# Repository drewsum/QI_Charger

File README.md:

# QI_Charger

A DIY QI Wireless Phone Charger with Digital Monitoring, OLED Display, and USB Virtual COM Port

Made with KiCad 5.0.2

Requires drewsum's 'KiCad_Custom_Libraries' git repository for custom symbols and footprints

Microcontroller U503 is programmed via header J401 using PIC KIT 3, with firmware located at sfw/U503_Firmware/QI_Monitor.X

Built with Microchip compiler XC8 V1.45, IDE MPLAB V5.15

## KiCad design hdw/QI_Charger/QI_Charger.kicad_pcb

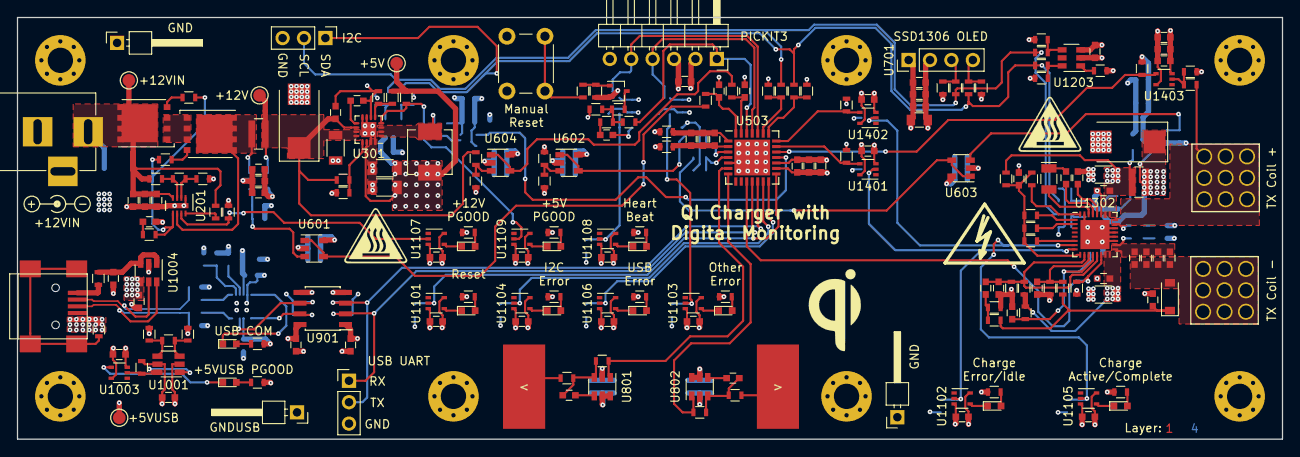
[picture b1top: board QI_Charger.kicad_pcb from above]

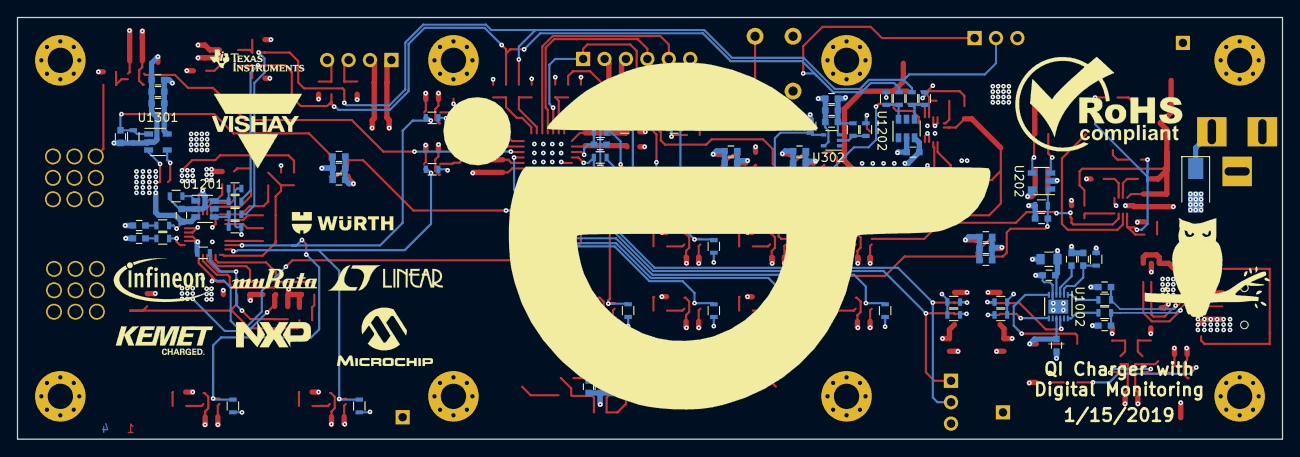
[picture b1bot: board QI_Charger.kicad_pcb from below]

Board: 4 copper layers, 150.0 x 50.0 mm, 305 parts (87 on the bottom side), 137 nets.

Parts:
C201, C204, C205, C303, C304, C401, C402, C501, C502, C503, C506, C601, C602, C609, C613, C701, C807, C808, C901, C902, C1001, C1002, C1003, C1004, C1005, C1007, C1008, C1011, C1101, C1102, C1103, C1104, C1105, C1106, C1107, C1108, C1109, C1201, C1202, C1203, C1301, C1309, C1311, C1314, C1316, C1401, C1403, C1404: 0.1uF; C_0603
C202, C206, C302, C305, C504, C507, C603, C604, C607, C608, C610, C612, C614, C616, C702, C801, C802, C805, C806, C1302, C1310, C1312, C1319, C1402: 10nF; C_0603
C203, C207, C208, C306, C505, C508, C605, C606, C611, C615, C703, C803, C804, C1303, C1304, C1306, C1317, C1405: 1nF; C_0603
C209, C1323: 100uF; CP_Tantalum_Case-X_EIA-7343-43_Reflow
C301: 10uF; C_1206
C307, C308, C1307, C1308: 22uF; C_1206
C704: 1uF; C_0805
C1006: 4.7uF; C_0805
C1009, C1010: 47pF; C_0603
C1305: 2.2pF; C_0603
C1313, C1315: 6.8nF; C_0603
C1318, C1322: 22nF; C_0603
C1320, C1321: 82nF; C_0603
D201: 24V; D_SMA
D1001, D1105, D1107, D1108, D1109: Green; LED_0603
D1002: Yellow; LED_0603
D1101, D1102, D1103, D1104, D1106: Red; LED_0603
D1301: MBR0530; D_SOD-123
H1501, H1502, H1503, H1504, H1505, H1506, H1507, H1508: 3mm Mounting Hole; MountingHole_3mm_Pad_Via
J201: +12V IN; BARREL_JACK
J401: PICKIT3; PICKIT3_Header
J701: I2C; Pin_Header_Straight_1x03_Pitch2.54mm
J901: UART; Pin_Header_Straight_1x03_Pitch2.54mm
J1001: USB_B_Mini; USB_Mini-B
J1301, J1302: PAD; Wuerth_7461096_M4_Shank_9pos
L301: 2.2u; L_Vishay_IHLP-2020
L501, L502, L1001, L1002: 600R 0.5A; L_0603
Q201, Q202: IPC100N04S51R7ATMA1; TDSON-8-1
Q401: BSS214NW; SOT-323_SC-70
R201: 6.04M; R_0603
R202: 86.6k; R_0603
R203: 243k; R_0603
R204, R302, R305, R1308, R1404: 100k; R_0603
R205, R206, R401: 10; R_0603
R207, R301, R308, R402, R404, R503, R504, R505, R506, R601, R602, R606, R703, R704, R901, R902, R903, R904, R1001, R1005, R1101, R1102, R1103, R1107, R1108, R1111, R1114, R1207, R1208, R1209, R1210, R1211, R1212, R1213, R1214, R1306, R1401, R1402, R1405, R1406, R1407: 10k; R_0603
R208, R607: 5.1k; R_0603
R209, R1303: 0.02; R_0612
R210: 499k; R_0603
R303, R306: 10.5k; R_0603
R304, R1304: 249k; R_0603
R307: 2k; R_0603
R403: 100; R_0603
R405, R501, R502, R701, R702, R803, R804, R1201, R1202, R1203, R1204, R1205, R1206: 0; R_0603
R406, R1006, R1009, R1104, R1105, R1106, R1109, R1110, R1112, R1113, R1115, R1116, R1403: 1k; R_0603
R603, R604, R605, R608, R801, R802: 499; R_0603
R1002: 487k; R_0603
R1003: 6.04k; R_0603
R1004: 40.2k; R_0603
R1007, R1008: 27; R_0603
R1301, R1302: 390k; R_0603
R1305: 47k; R_0603
R1307: 43k; R_0603
R1309: 130k; R_0603
R1310: 1M; R_0603
R1311, R1314, R1316: 15k; R_0603
R1312, R1313: 1; R_0603
R1315: 1.8k; R_0603
R1317: 27k; R_0603
SW401: MRST; SW_PUSH_6mm
SW801, SW802: Cap_Touch; Capacitive_Touch_Pad
TH1301: 100k; R_0603
TP201, TP204, TP1002: TP; Pin_Header_Angled_1x01_Pitch2.54mm
TP202, TP203, TP301, TP1001: TP; Test_Point
U201: LTC4365DDB; DFN-8-1EP_2x3mm_Pitch0.5mm
U202, U1301: INA138; SOT-23-5
U301: TPS62130; QFN-16-1EP_3x3mm_Pitch0.5mm
U302, U501, U502, U1403: 74LVC1G17; SOT-353_SC-70-5
U503: PIC18F27K40T-I_ML; QFN-28-1EP_6x6mm_Pitch0.65mm
U601, U602, U603, U604: OPA340NA; SOT-23-5
U701: SSD1306; Pin_Header_Straight_1x04_Pitch2.54mm
U801, U802: AT42QT1010-TSHR; SOT-23-6
U901: ISO7321C; SOIC-8_3.9x4.9mm_Pitch1.27mm
U1001: LT6700-1-S6; TSOT-23-6
U1002: FT234XD; DFN-12-1EP_3x3mm_Pitch0.45mm
U1003, U1101, U1103, U1104, U1106, U1107, U1108, U1109: 74LVC1G06; SOT-353_SC-70-5
U1004: TPD3S014DBVR; SOT-23-6
U1102, U1105: 74LVC1G07; SOT-353_SC-70-5
U1201, U1202, U1203: LM73-1; SOT-23-6
U1302: NXQ1TXH5_101J; QFN-32-1EP_5x5mm_Pitch0.5mm
U1401, U1402: 74LVC1G14; SOT-353_SC-70-5
Y1301: 32.768kHz; Crystal_SMD_G8-2pin_3.2x1.5mm

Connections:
+5V: C205.1, C206.1, C207.1, C304.1, C305.1, C306.1, C307.1, C308.1, C401.1, C502.1, C503.1, C506.1, C507.1, C508.1, C601.1, C602.1, C603.1, C604.1, C605.1, C606.1, C609.1, C610.1, C611.1, C613.1, C614.1, C615.1, C701.1, C702.1, C703.1, C704.1, C803.1, C804.1, C805.1, C806.1, C807.1, C808.1, C901.1, C1101.1, C1102.1, C1103.1, C1104.1, C1105.1, C1106.1, C1107.1, C1108.1, C1109.1, C1201.1, C1202.1, C1203.1, C1301.1, C1302.1, C1304.1, C1323.1, C1401.1, C1402.1, C1403.1, C1404.1, C1405.1, J401.2, L301.2, L501.2, R207.1, R301.1, R306.1, R404.1, R503.1, R504.1, R601.2, R703.1, R704.1, R901.2, R902.2, R1101.1, R1102.1, R1104.1, R1105.1, R1106.1, R1108.1, R1109.1, R1110.1, R1112.1, R1113.1, R1115.1, R1116.1, R1207.1, R1208.1, R1209.1, R1210.1, R1211.1, R1212.1, R1214.1, R1303.1, R1401.2, R1402.2, SW401.1, TP301.1, U202.5, U301.14, U302.5, U501.5, U502.5, U503.17, U601.5, U602.5, U603.5, U604.5, U701.1, U801.5, U801.6, U802.5, U802.6, U901.1, U1101.5, U1102.5, U1103.5, U1104.5, U1105.5, U1106.5, U1107.5, U1108.5, U1109.5, U1201.3, U1202.3, U1203.3, U1301.3, U1301.5, U1401.5, U1402.5, U1403.5
+5VADC: C501.1, C504.1, C505.1, L501.1, U503.2
+5VP: C1307.1, C1308.1, C1310.1, C1312.1, R1301.1, R1303.2, R1308.1, R1310.1, U1301.4, U1302.15, U1302.16, U1302.25, U1302.26
+5V_USB: C902.1, C1002.1, C1003.1, C1004.1, C1005.1, C1006.1, C1008.1, R903.2, R904.2, R1001.1, R1002.1, R1005.1, R1006.1, R1009.1, TP1001.1, U901.8, U1001.5, U1002.4, U1002.9, U1003.5, U1004.4
+12V: C209.1, C301.1, C303.1, R209.2, R302.1, R606.2, TP203.1, U202.4, U301.10, U301.11, U301.12
+12Vin: C201.1, C202.1, C203.1, D201.1, J201.1, Q201.5, R201.1, R204.1, TP202.1, U201.4
/Microcontroller/PIC_I2C_SCL: R502.1, R503.2, U503.23
/Microcontroller/PIC_I2C_SDA: R501.2, R504.2, U503.22
/OLED Display/OLED_I2C_SCL: R702.1, R703.2, U701.3
/OLED Display/OLED_I2C_SDA: R701.2, R704.2, U701.4
/Temperature Sensors/Temp1_I2C_SCL: R1202.1, R1207.2, U1201.4
/Temperature Sensors/Temp1_I2C_SDA: R1201.2, R1210.2, U1201.6
/Temperature Sensors/Temp2_I2C_SCL: R1204.1, R1208.2, U1202.4
/Temperature Sensors/Temp2_I2C_SDA: R1203.2, R1211.2, U1202.6
/Temperature Sensors/Temp3_I2C_SCL: R1206.1, R1209.2, U1203.4
/Temperature Sensors/Temp3_I2C_SDA: R1205.2, R1212.2, U1203.6
/USB UART Bridge/BRIDGE_USB+: R1007.2, U1002.12
/USB UART Bridge/BRIDGE_USB-: R1008.2, U1002.1
/USB UART Bridge/CONN_USB+: C1009.1, J1001.3, R1007.1, U1004.6
/USB UART Bridge/CONN_USB-: C1010.1, J1001.2, R1008.1, U1004.5
/USB UART Bridge/POS5_USB_PGOOD: R1005.2, U1001.1, U1001.6, U1003.2
Cap_Touch_Left: R803.2, U503.6, U801.1
Cap_Touch_Right: R804.2, U503.7, U802.1
GND: C201.2, C202.2, C203.2, C204.2, C205.2, C206.2, C207.2, C208.2, C209.2, C301.2, C302.2, C303.2, C304.2, C305.2, C306.2, C307.2, C308.2, C401.2, C402.2, C502.2, C503.2, C506.2, C507.2, C508.2, C601.2, C602.2, C603.2, C604.2, C605.2, C606.2, C607.2, C608.2, C609.2, C610.2, C611.2, C612.2, C613.2, C614.2, C615.2, C616.2, C701.2, C702.2, C703.2, C704.2, C803.2, C804.2, C805.2, C806.2, C807.2, C808.2, C901.2, C1101.2, C1102.2, C1103.2, C1104.2, C1105.2, C1106.2, C1107.2, C1108.2, C1109.2, C1201.2, C1202.2, C1203.2, C1301.2, C1302.2, C1303.2, C1304.2, C1306.2, C1307.2, C1308.2, C1309.2, C1310.2, C1311.2, C1312.2, C1313.2, C1315.2, C1317.2, C1318.2, C1322.2, C1323.2, C1401.2, C1402.2, C1403.2, C1404.2, C1405.2, D201.2, J201.2, J201.3, J401.3, J701.3, J901.3, L502.2, Q401.2, R203.2, R210.2, R303.2, R305.2, R307.2, R308.2, R402.2, R505.2, R506.2, R602.1, R607.2, R1103.2, R1107.2, R1111.2, R1114.2, R1213.2, R1304.2, R1306.2, R1311.2, R1314.2, R1315.2, R1404.2, R1405.2, R1406.1, R1407.1, TH1301.2, TP201.1, TP204.1, U201.1, U201.9, U202.2, U301.6, U301.7, U301.8, U301.15, U301.16, U301.17, U302.3, U501.3, U502.3, U503.5, U503.16, U503.29, U601.2, U602.2, U603.2, U604.2, U701.2, U801.2, U802.2, U901.4, U1101.3, U1102.3, U1103.3, U1104.3, U1105.3, U1106.3, U1107.3, U1108.3, U1109.3, U1201.2, U1202.2, U1203.2, U1301.2, U1302.19, U1302.20, U1302.21, U1302.22, U1302.27, U1302.31, U1302.33, U1401.3, U1402.3, U1403.3
GNDA: C501.2, C504.2, C505.2, L502.1, U503.1
GND_USB: C902.2, C1001.2, C1002.2, C1003.2, C1004.2, C1005.2, C1006.2, C1007.2, C1008.2, C1009.2, C1010.2, C1011.2, J1001.5, L1002.1, R1004.2, TP1002.1, U901.5, U1001.2, U1002.5, U1002.13, U1003.3, U1004.2
Heartbeat_LED: R505.1, R1114.1, U501.4, U1108.2
I2C_Error_LED: R1107.1, U503.13, U1104.2
I2C_SCL: J701.2, R502.2, R702.2, R1202.2, R1204.2, R1206.2
I2C_SDA: J701.1, R501.1, R701.1, R1201.1, R1203.1, R1205.1
ICSPCLK: J401.5, U501.2, U503.24
ICSPDAT: J401.4, U502.2, U503.25
unnamed: C204.1, R208.2
unnamed: C302.1, U301.9
unnamed: C402.1, R405.2
unnamed: C801.1, U801.4
unnamed: C801.2, R801.2, R803.1, U801.3
unnamed: C802.1, U802.4
unnamed: C802.2, R802.2, R804.1, U802.3
unnamed: C1001.1, R1001.2, U1002.2
unnamed: C1007.1, U1002.3
unnamed: C1011.1, L1001.2, U1004.1, U1004.3
unnamed: C1303.1, R1301.2, R1302.1, R1305.1, R1307.1, R1309.1, U1302.9
unnamed: C1305.2, Y1301.1
unnamed: C1309.1, U1302.28
unnamed: C1313.1, R1312.2
unnamed: C1314.1, C1316.1, C1320.1, C1321.1, D1301.2, J1302.1
unnamed: C1314.2, C1316.2, C1320.2, C1321.2, R1313.1, U1302.17, U1302.18
unnamed: C1315.1, R1313.2
unnamed: C1317.1, C1319.1, R1310.2, R1311.1, U1302.10, U1302.13
unnamed: C1318.1, R1315.1, R1317.2, U1302.11
unnamed: C1319.2, R1314.1, R1316.2
unnamed: C1322.1, D1301.1, R1316.1, R1317.1
unnamed: D1001.1, U1003.4
unnamed: D1001.2, R1006.2
unnamed: D1002.2, R1009.2
unnamed: D1101.1, U1101.4
unnamed: D1101.2, R1104.2
unnamed: D1102.1, U1102.4
unnamed: D1102.2, R1105.2
unnamed: D1103.1, U1103.4
unnamed: D1103.2, R1106.2
unnamed: D1104.1, U1104.4
unnamed: D1104.2, R1109.2
unnamed: D1105.1, U1105.4
unnamed: D1105.2, R1110.2
unnamed: D1106.1, U1106.4
unnamed: D1106.2, R1112.2
unnamed: D1107.1, U1107.4
unnamed: D1107.2, R1113.2
unnamed: D1108.1, U1108.4
unnamed: D1108.2, R1115.2
unnamed: D1109.1, U1109.4
unnamed: D1109.2, R1116.2
unnamed: J1001.1, L1001.1
unnamed: J1001.6, L1002.2
unnamed: L301.1, R304.1, U301.1, U301.2, U301.3
unnamed: Q201.1, Q201.2, Q201.3, Q202.1, Q202.2, Q202.3
unnamed: Q201.4, R205.2
unnamed: Q202.4, R206.1
unnamed: Q202.5, R209.1, U201.6, U202.3
unnamed: Q401.1, R401.2, R402.1
unnamed: Q401.3, R403.2
unnamed: R201.2, R202.1, U201.3
unnamed: R202.2, R203.1, U201.2
unnamed: R204.2, U201.8
unnamed: R205.1, R206.2, R208.1, U201.5
unnamed: R302.2, R303.1, U301.13
unnamed: R304.2, R305.1, U302.2
unnamed: R306.2, R307.1, U301.5
unnamed: R401.1, SW401.2
unnamed: R403.1, R404.2, R405.1, R406.2
unnamed: R601.1, R602.2, U602.3
unnamed: R603.2, U601.1, U601.4
unnamed: R604.2, U602.1, U602.4
unnamed: R605.2, U603.1, U603.4
unnamed: R606.1, R607.1, U604.3
unnamed: R608.2, U604.1, U604.4
unnamed: R801.1, SW801.1
unnamed: R802.1, SW802.1
unnamed: R1002.2, R1003.1, U1001.3
unnamed: R1003.2, R1004.1, U1001.4
unnamed: R1213.1, U1201.1
unnamed: R1214.2, U1203.1
unnamed: R1302.2, U1302.32
unnamed: R1305.2, U1302.1
unnamed: R1307.2, U1302.2
unnamed: R1309.2, U1302.6
unnamed: R1403.2, R1404.1, U1403.2
Other_Error_LED: R506.1, R1103.1, U502.4, U1103.2
POS5_ADC: C608.1, R604.1, U503.3
POS5_PGOOD: R301.2, U301.4, U1109.2
POS5_SW_SNS: R308.1, U302.4, U503.18
POS12_ADC: C616.1, R608.1, U503.27
POS12_ISNS: C208.1, R210.1, U202.1, U601.3
POS12_ISNS_ADC: C607.1, R603.1, U503.28
POS12_PGOOD: R207.2, U201.7, U1107.2
QI_Charge: R1407.2, U503.21, U1402.4
QI_ISNS: C1306.1, R1304.1, U603.3, U1301.1
QI_ISNS_ADC: C612.1, R605.1, U503.4
QI_Idle: R1406.2, U503.20, U1401.4
QI_LED_G: R1108.2, R1402.1, U1105.2, U1302.7, U1402.2
QI_LED_R: R1102.2, R1401.1, U1102.2, U1302.8, U1401.2
QI_NTC: C1311.1, R1308.2, TH1301.1, U1302.12
QI_OSC_1: C1305.1, U1302.29
QI_OSC_2: U1302.30, Y1301.2
QI_SW: J1301.1, R1312.1, R1403.1, U1302.23, U1302.24
QI_SW_SNS: R1405.1, U503.19, U1403.4
QI_Standby: R1306.1, U503.10, U1302.14
USB_Error_LED: R1111.1, U503.14, U1106.2
USB_UART_RX: J901.1, R901.1, U503.11, U901.2
USB_UART_RX_ISO: R904.1, U901.7, U1002.7
USB_UART_TX: J901.2, R902.1, U503.12, U901.3
USB_UART_TX_ISO: R903.1, U901.6, U1002.10
~ACTIVE_LED: R1101.2, U503.15, U1101.2
~MCLR: J401.1, R406.1, U503.26
~USB_ACTIVE: D1002.1, U1002.6

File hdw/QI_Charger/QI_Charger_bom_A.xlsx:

References | Value | Quantity Per PCB | Digi-Key PN
C201 C204 C205 C303 C304 C401 C402 C501 C502 C503 C506 C601 C602 C609 C613 C701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 | 0.1uF | 48 | 311-1344-1-ND
C209 C1323 | 100uF | 2 | 718-1102-1-ND
C202 C206 C302 C305 C504 C507 C603 C604 C607 C608 C610 C612 C614 C616 C702 C801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 | 10nF | 24 | 1276-1921-1-ND
C301 | 10uF | 1 | 1276-7031-1-ND
C203 C207 C208 C306 C505 C508 C605 C606 C611 C615 C703 C803 C804 C1303 C1304 C1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 | 1nF | 18 | 1276-1018-1-ND
C704 | 1uF | 1 | 490-1695-1-ND
C1305 | 2.2pF | 1 | 1276-1281-1-ND
C1318 C1322 | 22nF | 2 | 399-1280-1-ND
C307 C308 C1307 C1308 | 22uF | 4 | 1276-3148-1-ND
C1006 | 4.7uF | 1 | 1276-2972-1-ND
C1009 C1010 | 47pF | 2 | 478-1171-1-ND
C1313 C1315 | 6.8nF | 2 | 399-9121-1-ND
C1320 C1321 | 82nF | 2 | 478-10362-1-ND
D201 | 24V | 1 | SMAJ24CALFCT-ND
D1001 D1105 D1107 D1108 D1109 | Green | 5 | 160-1446-1-ND
D1301 | MBR0530 | 1 | MBR0530T1GOSCT-ND
D1101 D1102 D1103 D1104 D1106 | Red | 5 | 160-1447-1-ND
D1002 | Yellow | 1 | 160-1448-1-ND
DOC701 | 0x3C | 1
DOC1202 | 0x4C | 1
DOC1201 | 0x4D | 1
DOC1203 | 0x4F | 1
DOC1001 | COM_Port_Settings | 1
DOC501 | Master | 1
J201 | +12V IN | 1 | CP-202BH-ND
J1301 J1302 | PAD | 2 | 732-3214-ND
J401 | PICKIT3 | 1
J1001 | USB_B_Mini | 1 | 732-2109-1-ND
L301 | 2.2u | 1 | 541-1236-1-ND
L1301 | 6.3uH | 1 | 732-5284-ND
L501 L502 L1001 L1002 | 600R 0.5A | 4 | 732-2389-1-ND
MK1501 MK1502 MK1507 MK1508 MK1511 MK1512 MK1515 MK1516 | #4-40 Screw | 8 | 36-9900-ND
MK1503 MK1504 MK1505 MK1506 MK1509 MK1510 MK1513 MK1514 | #4-40 Standoff | 8 | 36-1892-ND
Q401 | BSS214NW | 1 | BSS214NWH6327XTSA1CT-ND
Q201 Q202 | IPC100N04S51R7ATMA1 | 2 | IPC100N04S51R7ATMA1CT-ND
R405 R501 R502 R701 R702 R803 R804 R1201 R1202 R1203 R1204 R1205 R1206 | 0 | 13 | 311-0.0GRCT-ND
R209 R1303 | 0.02 | 2 | P16010CT-ND
R1312 R1313 | 1 | 2 | 311-1.00HRCT-ND
R1315 | 1.8k | 1 | CR0603-FX-1801ELFCT-ND
R205 R206 R401 | 10 | 3 | YAG3351CT-ND
R303 R306 | 10.5k | 2 | 311-10.5KHRCT-ND
R403 | 100 | 1 | A106047CT-ND
R204 R302 R305 R1308 R1404 | 100k | 5 | A106046CT-ND
R207 R301 R308 R402 R404 R503 R504 R505 R506 R601 R602 R606 R703 R704 R901 R902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 | 10k | 41 | RMCF0603FT10K0CT-ND
R1309 | 130k | 1 | 311-130KHRCT-ND
R1311 R1314 R1316 | 15k | 3 | 311-15.0KHRCT-ND
R1310 | 1M | 1 | 311-1.00MHRCT-ND
R406 R1006 R1009 R1104 R1105 R1106 R1109 R1110 R1112 R1113 R1115 R1116 R1403 | 1k | 13 | RMCF0603FT1K00CT-ND
R203 | 243k | 1 | 311-243KHRCT-ND
R304 R1304 | 249k | 2 | RMCF0603FT249KCT-ND
R1007 R1008 | 27 | 2 | RMCF0603FT27R0CT-ND
R1317 | 27k | 1 | RMCF0603FT27K0CT-ND
R307 | 2k | 1 | 311-2.00KHRCT-ND
R1301 R1302 | 390k | 2 | 311-390KHRCT-ND
R1004 | 40.2k | 1 | 311-40.2KHRCT-ND
R1307 | 43k | 1 | 311-43.0KHRCT-ND
R1305 | 47k | 1 | 311-47.0KHRCT-ND
R1002 | 487k | 1 | 311-487KHRCT-ND
R603 R604 R605 R608 R801 R802 | 499 | 6 | P499HCT-ND
R210 | 499k | 1 | RMCF0603FT499KCT-ND
R208 R607 | 5.1k | 2 | YAG3621CT-ND
R201 | 6.04M | 1 | 541-6.04MHCT-ND
R201 | 6.04k | 1 | RMCF0603FT6K04CT-ND
R202 | 86.6k | 1 | 311-86.6KHRCT-ND
SW801 SW802 | Cap_Touch | 2
SW401 | MRST | 1
TH1301 | 100k | 1 | P10555CT-ND
U1003 U1101 U1104 U1106 U1107 U1108 U1109 1103 | 74LVC1G06 | 8 | 296-8484-1-ND
U1102 U1105 | 74LVC1G07 | 2 | 296-8486-1-ND
U1401 U1402 | 74LVC1G14 | 2 | 296-11608-1-ND
U302 U501 U502 U1403 | 74LVC1G17 | 4 | 296-11934-1-ND
U801 U802 | AT42QT1010-TSHR | 2 | AT42QT1010-TSHRCT-ND
U1002 | FT234XD | 1 | 768-1178-1-ND
U202 U1301 | INA138 | 2 | INA138NACT-ND
U901 | ISO7321C | 1 | 296-42102-1-ND
U1201 U1202 U1203 | LM73-1 | 3 | LM73CIMK-1/NOPBCT-ND
U1001 | LT6700-1-S6 | 1 | LT6700CS6-1#TRMPBFCT-ND
U201 | LTC4365DDB | 1 | LTC4365IDDB#TRMPBFCT-ND
U1302 | NXQ1TXH5_101J | 1 | 568-12937-1-ND
U601 U602 U603 U604 | OPA340NA | 4 | 296-26275-1-ND
U503 | PIC18F27K40T-I_ML | 1 | PIC18F27K40T-I/MLCT-ND
U701 | SSD1306 | 1
U1004 | TPD3S014DBVR | 1 | 296-38835-1-ND
U301 | TPS62130 | 1 | 296-37878-1-ND
Y1301 | 32.768kHz | 1 | G83270021CT-ND

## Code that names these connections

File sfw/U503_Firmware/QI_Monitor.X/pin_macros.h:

/* Microchip Technology Inc. and its subsidiaries.  You may use this software 
 * and any derivatives exclusively with Microchip products. 
 * 
 * THIS SOFTWARE IS SUPPLIED BY MICROCHIP "AS IS".  NO WARRANTIES, WHETHER 
 * EXPRESS, IMPLIED OR STATUTORY, APPLY TO THIS SOFTWARE, INCLUDING ANY IMPLIED 
 * WARRANTIES OF NON-INFRINGEMENT, MERCHANTABILITY, AND FITNESS FOR A 
 * PARTICULAR PURPOSE, OR ITS INTERACTION WITH MICROCHIP PRODUCTS, COMBINATION 
 * WITH ANY OTHER PRODUCTS, OR USE IN ANY APPLICATION. 
 *
 * IN NO EVENT WILL MICROCHIP BE LIABLE FOR ANY INDIRECT, SPECIAL, PUNITIVE, 
 * INCIDENTAL OR CONSEQUENTIAL LOSS, DAMAGE, COST OR EXPENSE OF ANY KIND 
 * WHATSOEVER RELATED TO THE SOFTWARE, HOWEVER CAUSED, EVEN IF MICROCHIP HAS 
 * BEEN ADVISED OF THE POSSIBILITY OR THE DAMAGES ARE FORESEEABLE.  TO THE 
 * FULLEST EXTENT ALLOWED BY LAW, MICROCHIP'S TOTAL LIABILITY ON ALL CLAIMS 
 * IN ANY WAY RELATED TO THIS SOFTWARE WILL NOT EXCEED THE AMOUNT OF FEES, IF 
 * ANY, THAT YOU HAVE PAID DIRECTLY TO MICROCHIP FOR THIS SOFTWARE.
 *
 * MICROCHIP PROVIDES THIS SOFTWARE CONDITIONALLY UPON YOUR ACCEPTANCE OF THESE 
 * TERMS. 
 */

/* 
 * File:   
 * Author: 
 * Comments:
 * Revision history: 
 */

// This is a guard condition so that contents of this file are not included
// more than once.  
#ifndef _PIN_MACROS_H
#define	_PIN_MACROS_H

#include <xc.h> // include processor files - each processor file is guarded.  

// These are pin macro definitions so that microcontroller I/O can be easily
// accessed instead of reading from/writing to bitfields in registers

// Port A
#define POS12_ADC_PIN           PORTAbits.RA0
#define POS12_ISNS_ADC_PIN      PORTAbits.RA1
#define POS5_ADC_PIN            PORTAbits.RA4
#define QI_ISNS_ADC_PIN         PORTAbits.RA5
#define CAP_TOUCH_RIGHT_PIN     PORTAbits.RA6
#define CAP_TOUCH_LECT_PIN      PORTAbits.RA7

// Port B
#define POS5_SW_SNS_PIN         PORTBbits.RB0
#define QI_SW_SNS_PIN           PORTBbits.RB1
#define QI_IDLE_PIN             PORTBbits.RB2
#define QI_IDLE_PIN_RISE        IOCBPbits.IOCBP2
#define QI_IDLE_PIN_FALL        IOCBNbits.IOCBN2
#define QI_CHARGE_PIN           PORTBbits.RB3
#define QI_CHARGE_PIN_RISE      IOCBPbits.IOCBP3
#define QI_CHARGE_PIN_FALL      IOCBNbits.IOCBN3
#define HEARTBEAT_LED_PIN       LATBbits.LATB6
#define OTHER_ERROR_LED_PIN     LATBbits.LATB7

// Port C
#define QI_STANDBY_PIN          LATCbits.LATC2
#define I2C_ERROR_LED_PIN       LATCbits.LATC5
#define USB_ERROR_LED_PIN       LATCbits.LATC6
#define nACTIVE_LED_PIN         LATCbits.LATC7


#endif	/* _PIN_MACROS_H */

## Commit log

2018-12-21 Edited .gitignore
2018-12-21 Added blank KiCad Project
2018-12-21 Added a few sheets
2018-12-21 Copied in USB sheet from earlier project
2018-12-21 Pulled in some status LEDs from previous project
2018-12-21 Changed all POS3P3 voltages to POS5
2018-12-21 Added microcontroller
2018-12-21 Added more to microcontroller and other sheets
2018-12-22 Added QI charge controller, some passives
2018-12-23 Added parts to QI controller page
2018-12-23 Added some QI interface circuitry
2018-12-27 Pulled in power input sheet from other project
2018-12-27 Added ADC and current sensing circuits
2018-12-28 Added a bunch of stuff to schematic
2018-12-28 Added cap touch sensors
2019-01-04 Pretty much finished schematic besides mounting holes
2019-01-04 Edited README
2019-01-07 Pulled in parts to PCB
2019-01-07 Fixed some footprint issues
2019-01-07 Arranged a lot of parts on PCB
2019-01-07 Placed more parts
2019-01-08 Added test points, arranged more parts on PCB
2019-01-09 Added mounting holes, board outline
2019-01-09 Finished initial placement of parts
2019-01-09 rearranged some parts, got rid of PIC crystal
2019-01-09 Added design rules, layer setup
2019-01-09 Started routing
2019-01-09 More routing
2019-01-10 Finished routing
2019-01-11 Added BOM
2019-01-14 Added communications test points
2019-01-15 Added a bunch of graphical items to PCB
2019-02-06 BOM changes, gitignore
2019-02-06 More ignoring
2019-02-06 even more ignoring
2019-02-06 Added basic mplab project
2019-02-06 Added main and interrupt manager files
2019-02-14 Added pin macros and terminal control
2019-02-15 Added more auto-generated code
2019-02-20 Added LOTs of firmware features, got the board working
2019-02-20 Fixed a few serial commands for clarity
2019-02-21 Added ADC firmware, temp and current sensors aren't working
2019-02-23 Added lots of ADC and calculation features
2019-02-23 Added die temp offset hack
2019-02-24 Added extensive error handling, I2C temp sensor stuff
2019-02-24 Trying to fix heartbeat glitch
2019-02-25 Added cap touch handler functions
2019-02-25 Added QI charge state detection, return to Idle not working
2019-02-27 Added TMR6 to return nxq_charge_state to Idle, now it won't set to charging afterward
2019-02-27 Got nxq_charge_state working, not sure about fully sharged state though
2019-02-27 Idle and charging work, error does not
2019-02-27 Got NXQ status working I think
2019-02-28 Got LM73 temp sensors working
2019-02-28 Got OLED working and full charge detection
2019-02-28 Added support for cap touch OLED screen selection
2019-02-28 Got OLED menus working, now LM73s are broken
2019-02-28 Resolved weird project config issues
2019-02-28 Added some variables to OLED screens
2019-03-01 Few edits
2019-03-01 Fixed charge detect bug, added OLED frames
2019-03-02 Added OLED Update optimizations
2019-03-03 Got FSW measurements working, kinda
2019-03-09 Modified lots of OLED stuff
2019-03-09 Fixed FSW serial commands
2019-03-10 Got charge error detection fixed
2019-03-10 Added QI charge time measurement
2019-03-11 Totally revised USB serial interface
2019-03-11 Added output charge and energy measurements
2019-03-11 Got live measurements working
2019-03-12 Live measurement updates optimizations
2019-03-12 Added better live measurements support
2019-03-13 Added NVM variables, mins and maxs
2019-03-13 Altered live message slightly
2019-03-13 Edited measurements message
2019-03-13 Few serial/OLED adjustments
2019-03-13 Cleaned up schematic
2019-03-13 Removed extra hdw files
2019-03-13 Removed more extra hdw files
2019-03-17 Edited a few OLED and serial messages
2019-03-18 A few string edits
2019-03-31 Edited a few serial interface strings
2019-03-31 More string edits
